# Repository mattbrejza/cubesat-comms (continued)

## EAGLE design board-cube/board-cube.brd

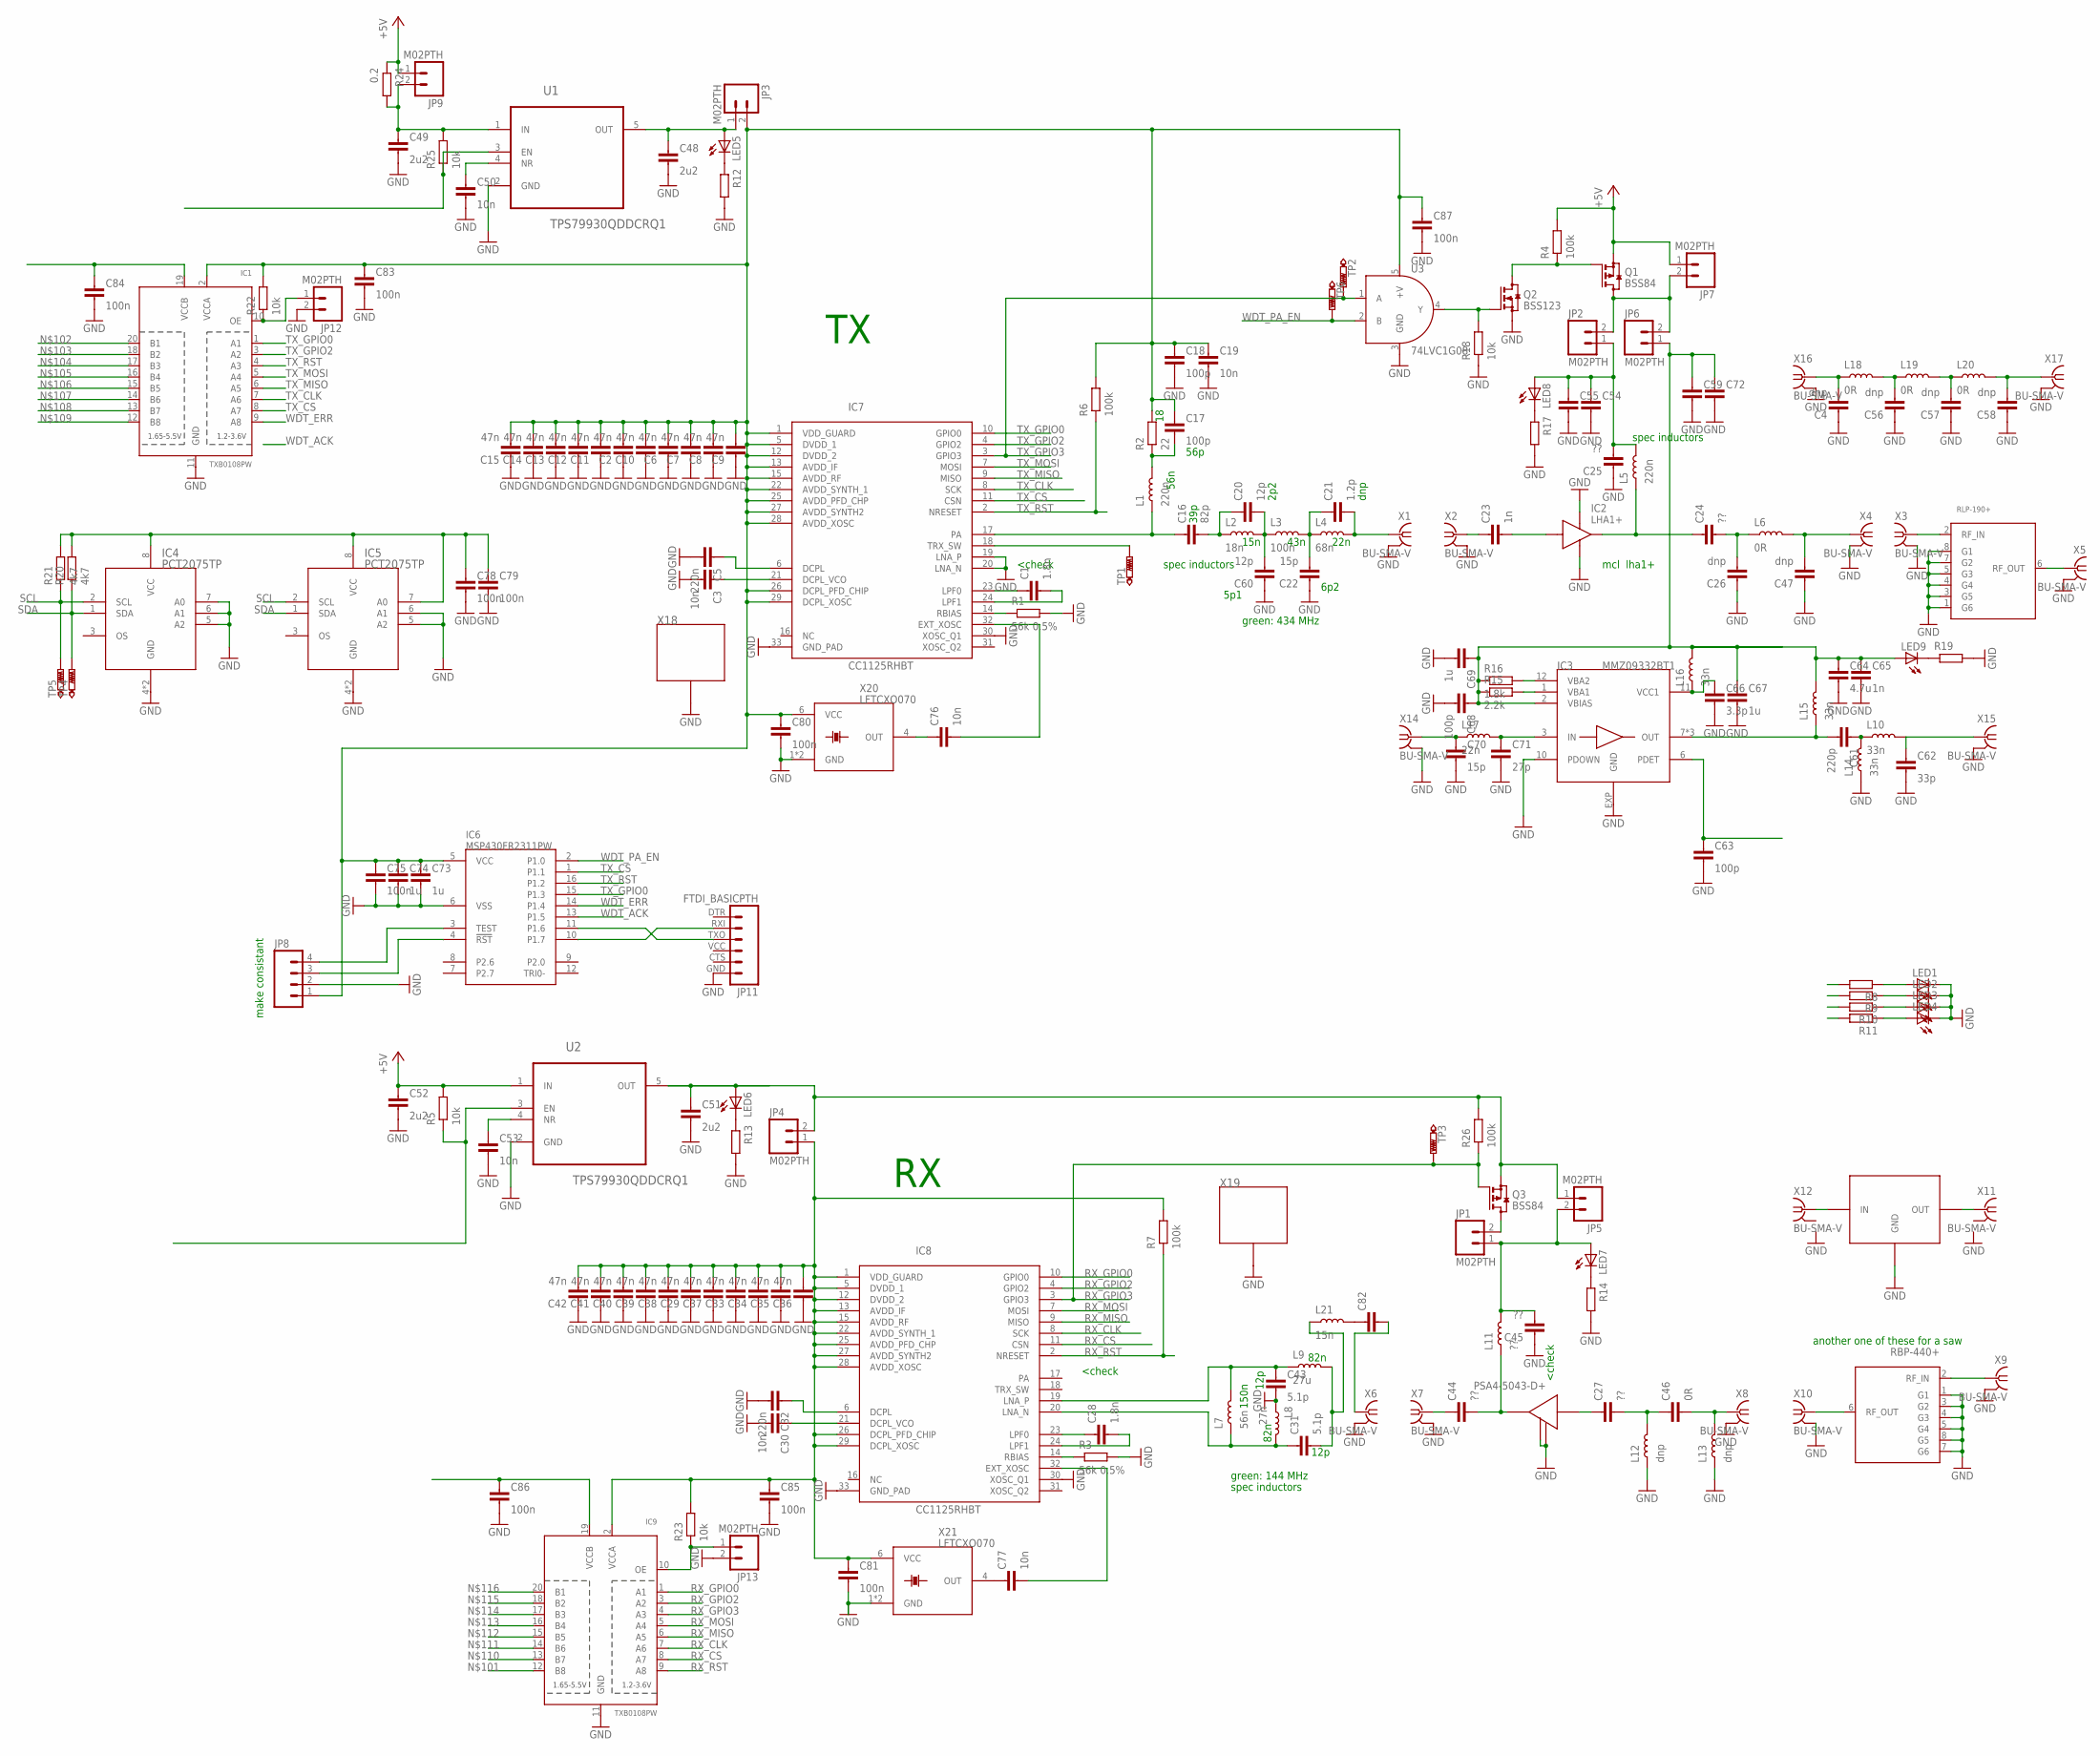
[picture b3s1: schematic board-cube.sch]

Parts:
C1, C28: 1.8n; C0603-N
C2, C6, C7, C8, C9, C10, C11, C12, C13, C14, C15, C29, C33, C34, C35, C36, C37, C38, C39, C40, C41, C42: 47n; C0603-N
C3, C19, C30, C50, C53, C76, C77: 10n; C0603-N
C4, C26, C47, C56, C57, C58: dnp; C0603-N
C5, C32: 220n; C0603-N
C16: 82p; C0603-N
C17, C18, C63, C68: 100p; C0603-N
C20, C60: 12p; C0603-N
C21: 1.2p; C0603-N
C22, C70: 15p; C0603-N
C23, C65: 1n; C0603-N
C24, C25, C27, C44, C45: ??; C0603-N
C31, C43: 5.1p; C0603-N
C46: 0R; C0603-N
C48, C49, C51, C52: 2u2; C0603-N
C54, C55, C59, C72: CAPACITOR0805-N; C0805-N
C61: 220p; C0603-N
C62: 33p; C0603-N
C64: 4.7u; C0603-N
C66: 3.3p; C0603-N
C67, C69, C73, C74: 1u; C0603-N
C71: 27p; C0603-N
C75, C78, C79, C80, C81, C83, C84, C85, C86, C87: 100n; C0603-N
C82: CAPACITOR0603-N; C0603-N
FL1: LPF_CS; PL-176
FL2: SAW_FILTER_CS; PL-176
FL3: GOLLEDGE_SAW_FILTER; GOLLEDGE_SAW
IC1, IC9: TXB0108PW; TSSOP20
IC2: LHA1+; PA
IC3: MMZ09332BT1; QFN3X3-6
IC4, IC5: PCT2075TP; HWSON8
IC6: MSP430FR2311PW; SSOP16
IC7, IC8: CC1125RHBT; QFN32_5X5
IC10: LNA_COMMON; LNA_MMM1362
JP1, JP2, JP3, JP4, JP5, JP6, JP7, JP9, JP12, JP13: M02PTH; 1X02
JP8: M04PTH; 1X04
JP11: FTDI_BASICPTH; FTDI_BASIC
L1, L5: 220n; L0603-N
L2: 18n; L0603-N
L3: 100n; L0603-N
L4: 68n; L0603-N
L6, L18, L19, L20: 0R; L0603-N
L7: 56n; L0603-N
L8: 27n; L0603-N
L9: 27u; L0603-N
L10, L14, L15, L16: 33n; L0603-N
L11: ??; L0603-N
L12, L13: dnp; L0603-N
L17: 22n; L0603-N
L21: 15n; L0603-N
LED1, LED2, LED3, LED4, LED5, LED6, LED7, LED8, LED9: LEDCHIP-LED0603; CHIP-LED0603
Q1, Q3: BSS84; SOT23
Q2: BSS123; SOT23
R1, R3: 56k 0.5%; R0603-N
R2: 22; R0603-N
R4, R6, R7, R26: 100k; R0603-N
R5, R18, R22, R23, R25: 10k; R0603-N
R8, R9, R10, R11, R12, R13, R14, R17, R19: RESISTOR0603-N; R0603-N
R15: 2.2k; R0603-N
R16: 1.8k; R0603-N
R20, R21: 4k7; R0603-N
R24: 0.2; R0603-N
TP1, TP2, TP3, TP4, TP5, TP6: PTR1B1,27; B1,27
U1, U2: TPS79930QDDCRQ1; SOT95P280X110-5N
U3: 74LVC1G08; SOT23-5
X1, X2, X3, X4, X5, X6, X7, X8, X9, X10, X11, X12, X14, X15, X16, X17: BU-SMA-V
X18, X19: SHIELD-26X26
X20, X21: LFTCXO070; 260-SERIES

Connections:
+5V: C52.1, JP7.1, JP9.1, Q1.2 (S), R4.2, R5.2, R24.1, U2.1 (IN)
GND: C2.1, C3.2, C4.1, C5.2, C6.1, C7.1, C8.1, C9.1, C10.1, C11.1, C12.1, C13.1, C14.1, C15.1, C18.2, C19.2, C22.1, C25.1, C26.1, C29.1, C30.2, C32.2, C33.1, C34.1, C35.1, C36.1, C37.1, C38.1, C39.1, C40.1, C41.1, C42.1, C43.2, C45.1, C47.1, C48.2, C49.2, C50.2, C51.2, C52.2, C53.2, C54.2, C55.2, C56.1, C57.1, C58.1, C59.2, C60.1, C62.2, C63.2, C64.2, C65.2, C66.2, C67.2, C68.2, C69.2, C70.2, C71.2, C72.2, C73.2, C74.2, C75.2, C78.2, C79.2, C80.2, C81.2, C83.2, C84.2, C85.2, C86.2, C87.2, FL1.1 (G6), FL1.3 (G5), FL1.4 (G4), FL1.5 (G3), FL1.7 (G2), FL1.8 (G1), FL2.1 (G1), FL2.3 (G2), FL2.4 (G3), FL2.5 (G4), FL2.7 (G6), FL2.8 (G5), FL3.A (GND), FL3.C (GND), FL3.D (GND), FL3.F (GND), IC1.11 (GND), IC2.GND1, IC2.GND2, IC3.10 (PDOWN), IC3.EXP (GND), IC4.4 (GND), IC4.5 (A2), IC4.6 (A1), IC4.7 (A0), IC4.EP (GND), IC5.4 (GND), IC5.5 (A2), IC5.6 (A1), IC5.EP (GND), IC6.6 (VSS), IC7.19 (LNA_P), IC7.20 (LNA_N), IC7.30 (XOSC_Q1), IC7.33 (GND_PAD), IC8.30 (XOSC_Q1), IC8.33 (GND_PAD), IC9.11 (GND), IC10.2, IC10.4, JP8.2, JP11.GND (6), JP12.2, JP13.2, L8.1, L12.1, L13.1, L14.1, LED1.C, LED2.C, LED3.C, LED4.C, Q2.2 (S), R1.2, R3.2, R12.2, R13.2, R14.2, R17.2, R18.1, R19.2, U1.2 (GND), U2.2 (GND), U3.3 (GND), X1.2, X1.3 (2), X1.4 (2), X1.5 (2), X2.2, X2.3 (2), X2.4 (2), X2.5 (2), X3.2, X3.3 (2), X3.4 (2), X3.5 (2), X4.2, X4.3 (2), X4.4 (2), X4.5 (2), X5.2, X5.3 (2), X5.4 (2), X5.5 (2), X6.2, X6.3 (2), X6.4 (2), X6.5 (2), X7.2, X7.3 (2), X7.4 (2), X7.5 (2), X8.2, X8.3 (2), X8.4 (2), X8.5 (2), X9.2, X9.3 (2), X9.4 (2), X9.5 (2), X10.2, X10.3 (2), X10.4 (2), X10.5 (2), X14.2, X14.3 (2), X14.4 (2), X14.5 (2), X15.2, X15.3 (2), X15.4 (2), X15.5 (2), X16.2, X16.3 (2), X16.4 (2), X16.5 (2), X17.2, X17.3 (2), X17.4 (2), X17.5 (2), X18.G1, X18.G2, X18.G3, X18.G4, X18.G5, X18.G6, X18.G7, X18.G8, X18.G9, X18.G10, X18.G11, X18.G12, X18.G13, X18.G14, X18.G15, X18.G16, X18.G17, X18.G19, X18.G20, X18.G21, X19.G1, X19.G2, X19.G3, X19.G4, X19.G5, X19.G6, X19.G7, X19.G8, X19.G9, X19.G10, X19.G11, X19.G12, X19.G13, X19.G14, X19.G15, X19.G16, X19.G17, X19.G19, X19.G20, X19.G21, X20.1 (GND), X20.3 (GND), X21.1 (GND), X21.3 (GND)
unnamed: C1.1, IC7.23 (LPF0)
unnamed: C1.2, IC7.24 (LPF1)
unnamed: C23.2, IC2.RF_IN
unnamed: C3.1, IC7.21 (DCPL_VCO)
unnamed: C17.2, L1.2, R2.1
unnamed: JP2.2, JP6.2, JP7.2, Q1.3 (D)
unnamed: C16.1, IC7.17 (PA), L1.1
unnamed: IC7.14 (RBIAS), R1.1
unnamed: C76.2, IC7.32 (EXT_XOSC)
unnamed: LED1.A, R8.1
unnamed: LED2.A, R9.1
unnamed: LED3.A, R10.1
unnamed: IC7.18 (TRX_SW), TP1.TP
unnamed: LED4.A, R11.1
unnamed: C4.2, L18.1, X16.1
unnamed: C24.1, IC2.RF_OUT, L5.1
unnamed: C5.1, IC7.6 (DCPL)
unnamed: C16.2, C20.1, L2.1
unnamed: C20.2, C60.2, L2.2, L3.1
unnamed: C21.1, C22.2, L3.2, L4.1
unnamed: C21.2, L4.2, X1.1
unnamed: C59.1, C64.1, C65.1, C67.1, C68.1, C69.1, C72.1, IC3.2 (VBIAS), JP6.1, L15.2, L16.2, LED9.A, R15.1, R16.1
unnamed: C24.2, C26.2, L6.1
unnamed: C23.1, X2.1
unnamed: C47.2, L6.2, X4.1
unnamed: FL1.2 (RF_IN), X3.1
unnamed: FL1.6 (RF_OUT), X5.1
unnamed: C28.1, IC8.23 (LPF0)
unnamed: C28.2, IC8.24 (LPF1)
unnamed: C30.1, IC8.21 (DCPL_VCO)
unnamed: C44.1, X7.1
unnamed: C44.2, IC10.1 (RF_OUT), L11.1
unnamed: IC8.14 (RBIAS), R3.1
unnamed: C77.2, IC8.32 (EXT_XOSC)
unnamed: C48.1, JP3.1, LED5.A, U1.5 (OUT)
unnamed: LED5.C, R12.1
unnamed: LED6.C, R13.1
unnamed: LED7.C, R14.1
unnamed: FL3.E (OUT), X11.1
unnamed: FL3.B (IN), X12.1
unnamed: C32.1, IC8.6 (DCPL)
unnamed: C27.1, IC10.3 (RF_IN)
unnamed: C43.1, IC8.19 (LNA_P), L7.2, L9.1
unnamed: C31.1, IC8.20 (LNA_N), L7.1, L8.2
unnamed: C82.2, X6.1
unnamed: C27.2, C46.1, L12.2
unnamed: C2.2, C6.2, C7.2, C8.2, C9.2, C10.2, C11.2, C12.2, C13.2, C14.2, C15.2, C17.1, C18.1, C19.1, C73.1, C74.1, C75.1, C80.1, C83.1, C87.1, IC1.2 (VCCA), IC6.5 (VCC), IC7.1 (VDD_GUARD), IC7.5 (DVDD_1), IC7.12 (DVDD_2), IC7.13 (AVDD_IF), IC7.15 (AVDD_RF), IC7.22 (AVDD_SYNTH_1), IC7.25 (AVDD_PFD_CHP), IC7.26 (DCPL_PFD_CHIP), IC7.27 (AVDD_SYNTH2), IC7.28 (AVDD_XOSC), IC7.29 (DCPL_XOSC), JP3.2, JP8.1, R2.2, R6.2, R22.2, U3.5 (+V), X20.6 (VCC)
unnamed: C45.2, JP1.1, JP5.2, L11.2, LED7.A
unnamed: JP4.2, JP5.1, LED6.A, Q3.2 (S), R26.2
unnamed: C46.2, L13.2, X8.1
unnamed: FL2.2 (RF_IN), X9.1
unnamed: FL2.6 (RF_OUT), X10.1
unnamed: C50.1, U1.4 (NR)
unnamed: C61.1, L10.1, L14.2
unnamed: C51.1, U2.5 (OUT)
unnamed: C53.1, U2.4 (NR)
unnamed: R5.1, U2.3 (EN)
unnamed: Q1.1 (G), Q2.3 (D), R4.1
unnamed: C29.2, C33.2, C34.2, C35.2, C36.2, C37.2, C38.2, C39.2, C40.2, C41.2, C42.2, C81.1, C85.1, IC8.1 (VDD_GUARD), IC8.5 (DVDD_1), IC8.12 (DVDD_2), IC8.13 (AVDD_IF), IC8.15 (AVDD_RF), IC8.22 (AVDD_SYNTH_1), IC8.25 (AVDD_PFD_CHP), IC8.26 (DCPL_PFD_CHIP), IC8.27 (AVDD_SYNTH2), IC8.28 (AVDD_XOSC), IC8.29 (DCPL_XOSC), IC9.2 (VCCA), JP4.1, R7.2, R23.2, X21.6 (VCC)
unnamed: C61.2, IC3.7 (OUT), IC3.8 (OUT), IC3.9 (OUT), L15.1
unnamed: C62.1, L10.2, X15.1
unnamed: C63.1, IC3.6 (PDET)
unnamed: LED8.C, R17.1
unnamed: C66.1, IC3.11 (VCC1), L16.1
unnamed: C49.1, JP9.2, R24.2, R25.2, U1.1 (IN)
unnamed: IC3.12 (VBA2), R16.2
unnamed: IC3.1 (VBA1), R15.2
unnamed: LED9.C, R19.1
unnamed: C70.1, L17.1, X14.1
unnamed: C71.1, IC3.3 (IN), L17.2
unnamed: JP1.2, Q3.3 (D)
unnamed: C56.2, L18.2, L19.1
unnamed: C57.2, L19.2, L20.1
unnamed: C58.2, L20.2, X17.1
unnamed: C25.2, C54.1, C55.1, JP2.1, L5.2, LED8.A
unnamed: IC1.10 (OE), JP12.1, R22.1
unnamed: C76.1, X20.4 (OUT)
unnamed: C77.1, X21.4 (OUT)
unnamed: IC6.3 (TEST), JP8.4
unnamed: IC6.4 (!RST), JP8.3
unnamed: IC6.11 (P1.6), JP11.TXO (3)
unnamed: C78.1, C79.1, IC4.8 (VCC), IC5.7 (A0), IC5.8 (VCC), R20.2, R21.2
unnamed: IC6.10 (P1.7), JP11.RXI (2)
unnamed: C82.1, L21.2
unnamed: C31.2, L9.2, L21.1
unnamed: IC9.10 (OE), JP13.1, R23.1
unnamed: C84.1, IC1.19 (VCCB)
unnamed: C86.1, IC9.19 (VCCB)
unnamed: R25.1, U1.3 (EN)
unnamed: Q2.1 (G), R18.2, U3.4 (Y)
RX_CLK: IC8.8 (SCK), IC9.7 (A6)
RX_CS: IC8.11 (CSN), IC9.8 (A7)
RX_GPIO0: IC8.10 (GPIO0), IC9.1 (A1)
RX_GPIO2: IC8.4 (GPIO2), IC9.3 (A2)
RX_GPIO3: IC8.3 (GPIO3), IC9.4 (A3), Q3.1 (G), R26.1, TP3.TP
RX_MISO: IC8.9 (MISO), IC9.6 (A5)
RX_MOSI: IC8.7 (MOSI), IC9.5 (A4)
RX_RST: IC8.2 (NRESET), IC9.9 (A8), R7.1
SCL: IC4.2 (SCL), IC5.2 (SCL), R21.1, TP5.TP
SDA: IC4.1 (SDA), IC5.1 (SDA), R20.1, TP4.TP
TX_CLK: IC1.7 (A6), IC7.8 (SCK)
TX_CS: IC1.8 (A7), IC6.1 (P1.1), IC7.11 (CSN)
TX_GPIO0: IC1.1 (A1), IC6.15 (P1.3), IC7.10 (GPIO0)
TX_GPIO2: IC1.3 (A2), IC7.4 (GPIO2)
TX_GPIO3: IC7.3 (GPIO3), TP2.TP, U3.1 (A)
TX_MISO: IC1.6 (A5), IC7.9 (MISO)
TX_MOSI: IC1.5 (A4), IC7.7 (MOSI)
TX_RST: IC1.4 (A3), IC6.16 (P1.2), IC7.2 (NRESET), R6.1
WDT_ACK: IC6.13 (P1.5)
WDT_ERR: IC1.9 (A8), IC6.14 (P1.4)
WDT_PA_EN: IC6.2 (P1.0), TP6.TP, U3.2 (B)

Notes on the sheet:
spec inductors
<check
another one of these for a saw
mcl lha1+
make consistant
5p1
150n
82n
12p
green: 144 MHz
56n
56p
39p
2p2
6p2
15n
43n
22n
dnp
green: 434 MHz

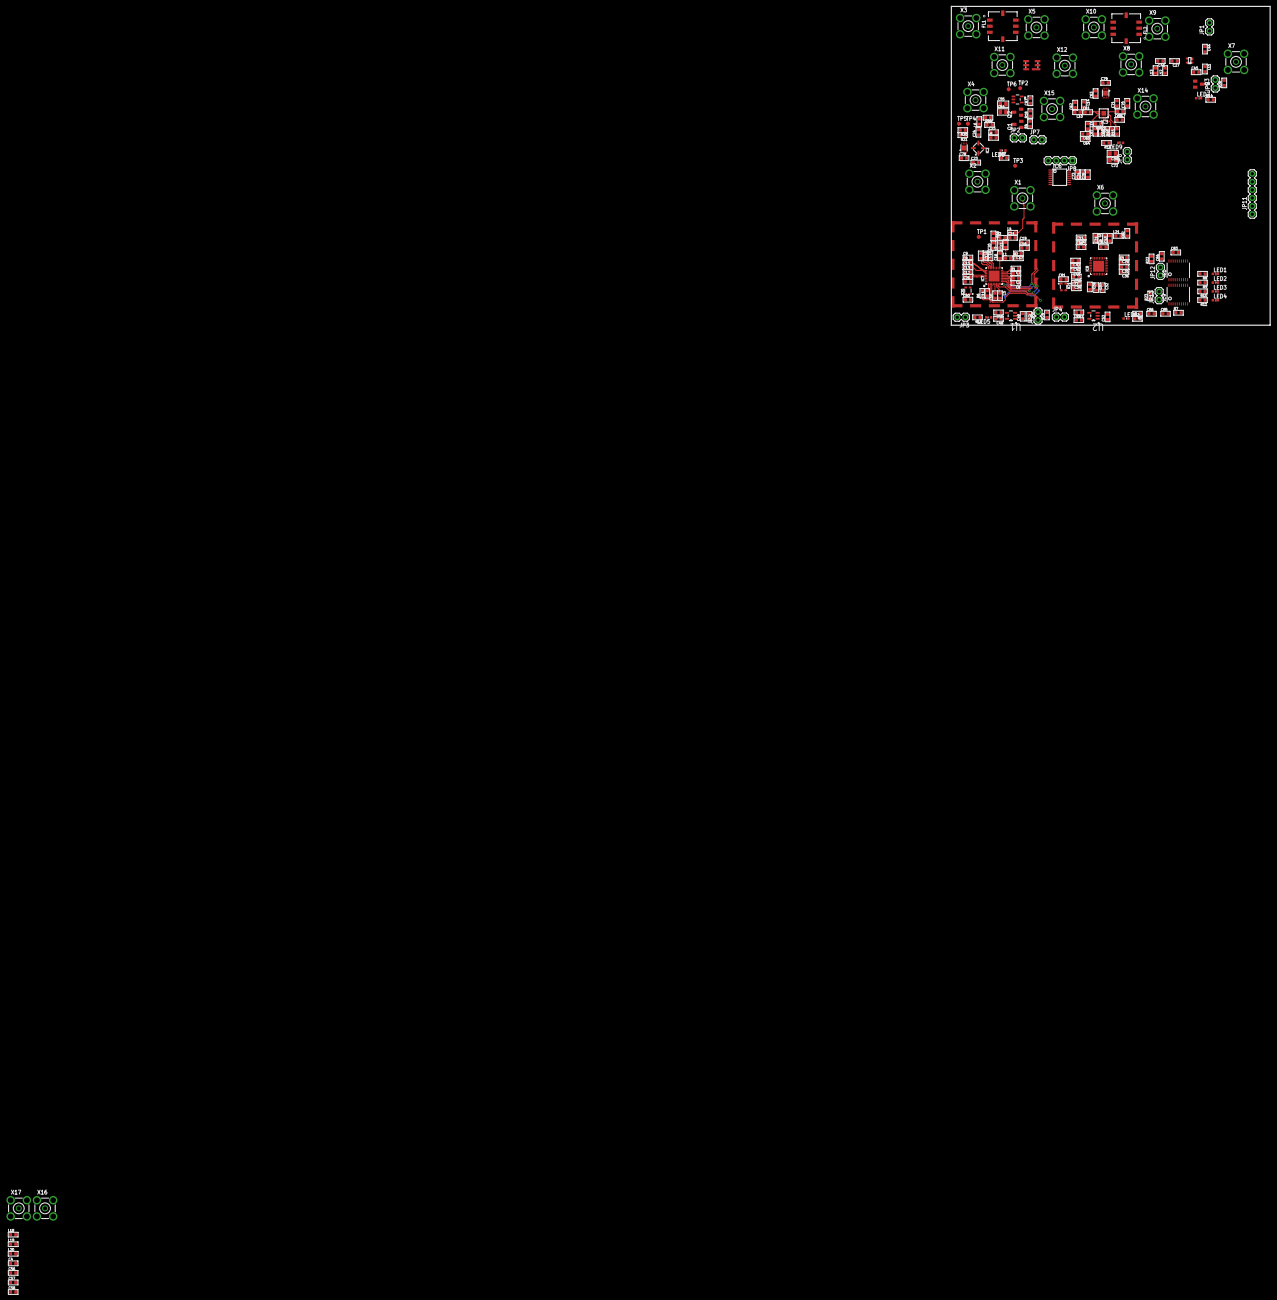
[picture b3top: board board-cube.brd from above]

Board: 4 copper layers, 100.0 x 100.0 mm, 200 parts (0 on the bottom side), 112 nets.

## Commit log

2016-03-22 more work
2016-03-23 enabling 4 layer
2016-06-08 Add Ava.lbr submodule for 434MHz SAW footprint.
2016-06-08 Add 434MHz SAW and 2x SMA Connectors to sch,lbr.
2016-10-23 added alternate PA
2016-10-23 adding supervising processor
2016-10-23 rough placement of PA
2016-10-25 fixing filter pin 1 dot
2016-10-25 updated footprints from modified library
2016-10-26 adding shielding can
2016-10-26 adding tcxo and temp sensor
2016-10-27 updating footprints and values, changing msp watchdog part
2016-10-31 added level shifter
2016-11-01 Fix PSA5043 LNA footprint.
2016-11-04 moving things around to fit better
2016-11-05 most digital signals wired up
2016-11-07 moving some parts around
2016-11-25 inital fig commit
2016-11-29 minor fig improvements
2016-12-12 added merged board
2016-12-12 added outline and corrected header locations
2016-12-12 more placement
2016-12-17 add digital wired up
2016-12-17 started routing
2016-12-19 more routing
2016-12-29 some more routing
2016-12-29 cleaning up silk
2016-12-29 almost done
2017-01-12 fixing resist issue on the m4
2017-01-21 adjusted crystal footprints
2017-03-15 sent off
2017-07-29 adding images
2018-06-30 finishing off balun obard
2018-07-24 starting v2 of the board
2018-10-14 adding fram, some routing
2018-10-14 most routing done, still some queries remain
2018-10-21 added camera header, RF connectors, some cleanup
2018-10-24 switching to lha1+, camera rx/tx done
2018-11-06 adding gerbers
